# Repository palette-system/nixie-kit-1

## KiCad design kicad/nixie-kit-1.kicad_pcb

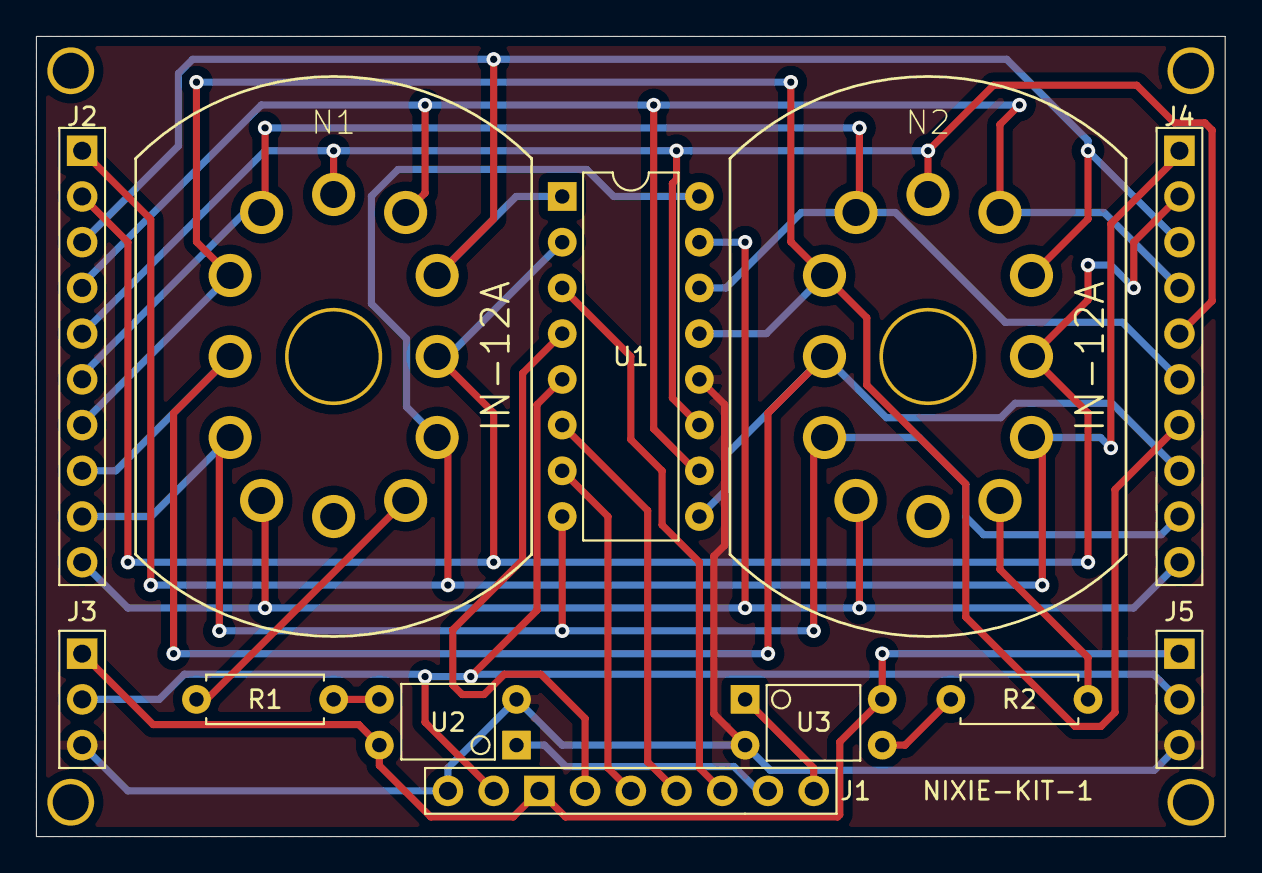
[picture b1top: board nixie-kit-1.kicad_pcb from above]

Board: 2 copper layers, 66.0 x 44.4 mm, 14 parts (0 on the bottom side), 23 nets.

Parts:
J1: nixie_on; PinHeader_1x02_P2.54mm_Vertical
J1#2: driver_con; PinHeader_1x04_P2.54mm_Vertical
J2, J3: dc_1; PinHeader_1x03_P2.54mm_Vertical
J2#2: nixie_con_1; PinHeader_1x10_P2.54mm_Vertical
J4: nixie_con_2; PinHeader_1x10_P2.54mm_Vertical
J5: dc_2; PinHeader_1x03_P2.54mm_Vertical
N1, N2: IN-12A; russian-nixies-IN-12
R1, R2: R_US; R_Axial_DIN0207_L6.3mm_D2.5mm_P7.62mm_Horizontal
U1: 74141; DIP-16_W7.62mm
U2, U3: TLP627; DIP-4_W7.62mm

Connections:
GND: J2.3, J3.3, J5.3, U1.12, U2.2, U3.2
unnamed: J1#2.1, U1.3
unnamed: J1#2.2, U1.6
unnamed: J1#2.3, U1.7
unnamed: J1#2.4, U1.4
unnamed: J2.1, J3.1, J5.1, U2.4, U3.4
unnamed: J2#2.1, J4.1, N1.0, N2.0, U1.16
unnamed: J2#2.2, J4.2, N1.9, N2.9, U1.2
unnamed: J2#2.3, J4.3, N1.8, N2.8, U1.1
unnamed: J2#2.4, J4.4, N1.7, N2.7, U1.10
unnamed: J2#2.5, J4.5, N1.6, N2.6, U1.11
unnamed: J2#2.6, J4.6, N1.5, N2.5, U1.14
unnamed: J2#2.7, J4.7, N1.4, N2.4, U1.13
unnamed: J2#2.8, J4.8, N1.3, N2.3, U1.9
unnamed: J2#2.9, J4.9, N1.2, N2.2, U1.8
unnamed: J2#2.10, J4.10, N1.1, N2.1, U1.15
unnamed: J1.1, U3.1
unnamed: J1.2, U2.1
unnamed: N1.A, R1.2
unnamed: N2.A, R2.2
unnamed: R1.1, U2.3
unnamed: R2.1, U3.3
VCC: J2.2, J3.2, J5.2, U1.5

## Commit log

2021-12-10 nixie-kit-1
